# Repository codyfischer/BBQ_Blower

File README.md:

# BBQ_Blower
PCB to control relays, mosfet's, measure temperature wirelessly using ESP8266 and Lora Wan

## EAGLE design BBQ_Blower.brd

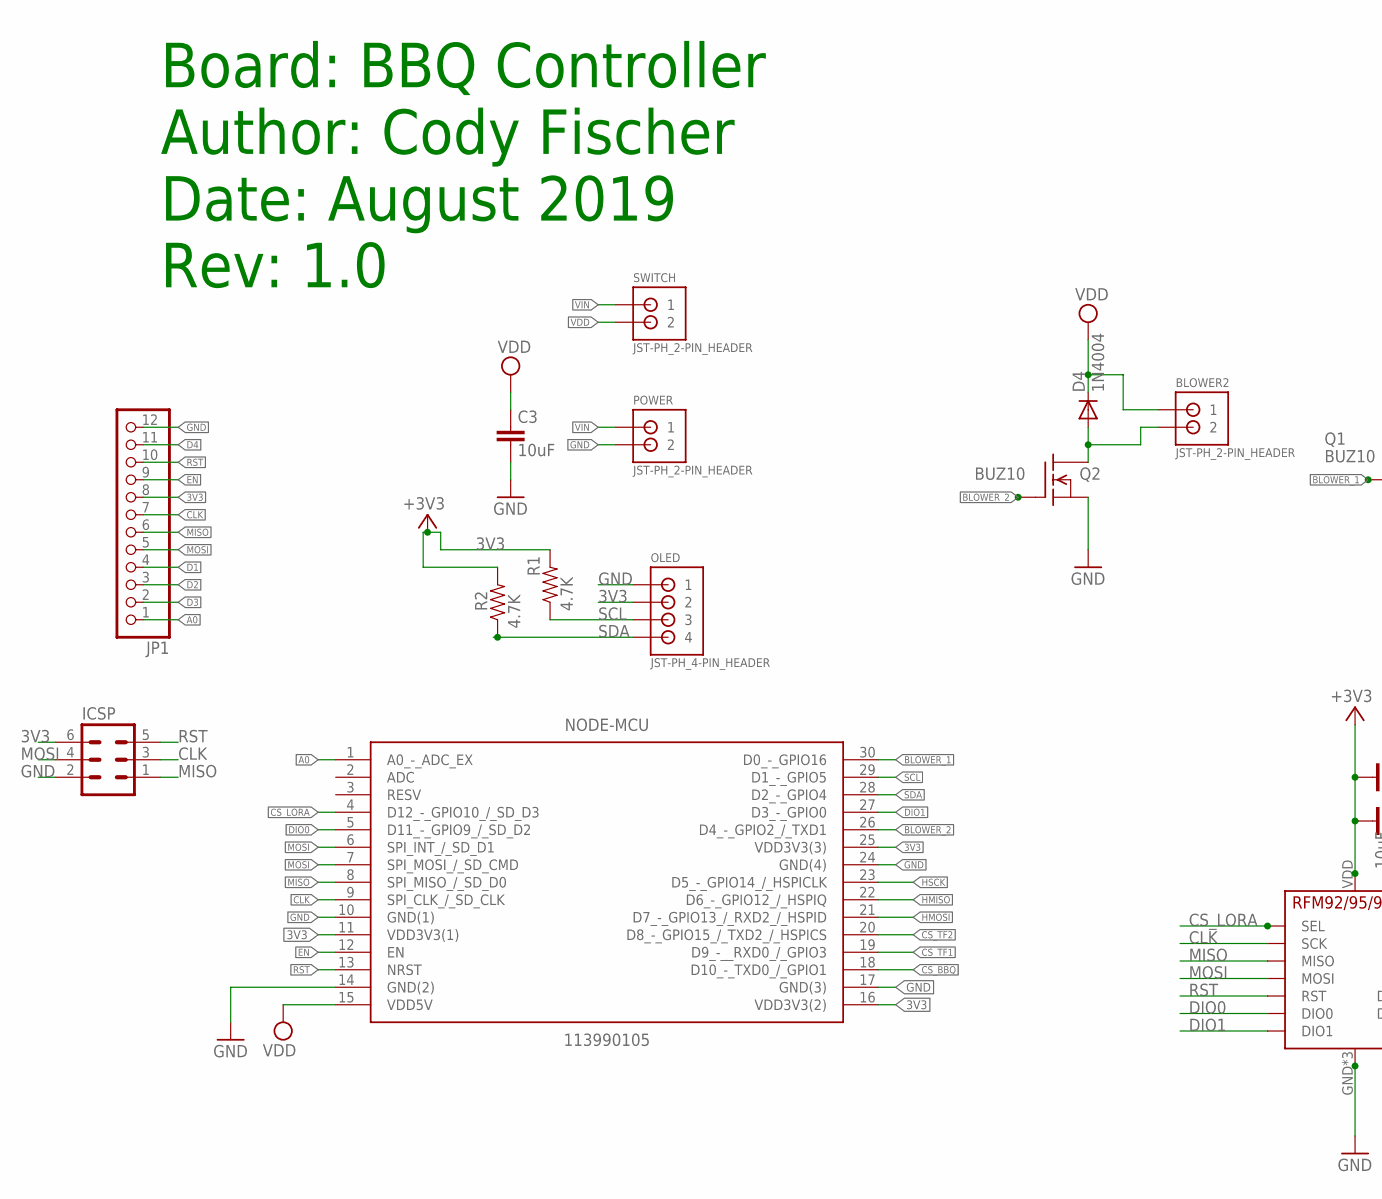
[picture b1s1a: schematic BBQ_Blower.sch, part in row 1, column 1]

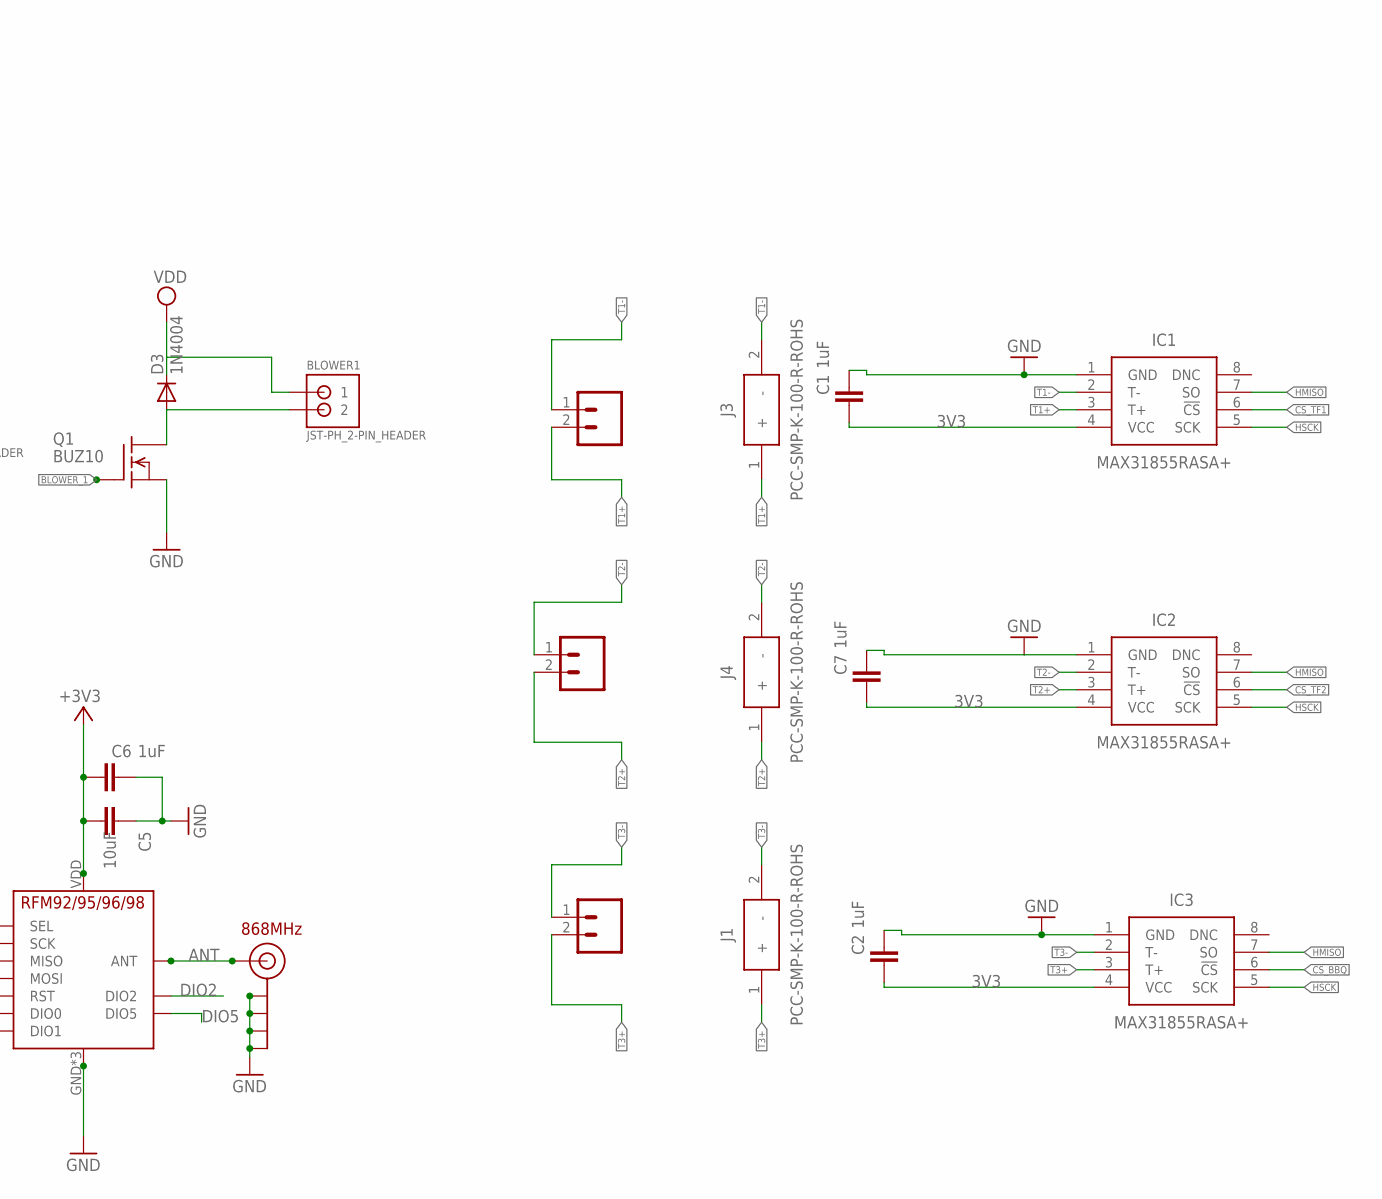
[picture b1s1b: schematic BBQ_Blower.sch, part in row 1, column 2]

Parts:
BLOWER1, BLOWER2: JST-PH_2-PIN_HEADER; JST_B2B-PH_HEADER
C1, C2, C6, C7: 1uF; C0805K
C3: 10uF; C025-050X050
C5: 10uF; C0805K
D3, D4: 1N4004; DO41-10
IC1, IC2, IC3: MAX31855RASA+; SOIC127P600X175-8N
ICSP: MA03-2
J1, J3, J4: PCC-SMP-K-100-R-ROHS; PCC-SMP
J$2: ANTENNATINY; SMA_UFL_PAD_TINY
JP1: PINHD-1X12; 1X12
NODE-MCU: 113990105; DIP2286W64P254L4826H735Q30N
OLED: JST-PH_4-PIN_HEADER; JST_B4B-PH_HEADER
POWER: JST-PH_2-PIN_HEADER; JST_B2B-PH_HEADER
Q1, Q2: BUZ10; TO220
R1, R2: 4.7K; 0805-RES
SWITCH: JST-PH_2-PIN_HEADER; JST_B2B-PH_HEADER
TH1, TH2, TH3: CONN_025MM; SCREWTERMINAL-5MM-2
U$5: RFM95

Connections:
3V3: C1.2, C2.2, C5.2, C6.2, C7.2, IC1.4 (VCC), IC2.4 (VCC), IC3.4 (VCC), ICSP.6, JP1.8, NODE-MCU.11 (VDD3V3(1)), NODE-MCU.16 (VDD3V3(2)), NODE-MCU.25 (VDD3V3(3)), OLED.P2 (2), R1.2, R2.2, U$5.VDD (VCC)
A0: JP1.1, NODE-MCU.1 (A0_-_ADC_EX)
ANT: J$2.ANT1 (SIGNAL), J$2.ANT2 (SIGNAL), J$2.ANT3 (SIGNAL), U$5.ANT
BLOWER1: BLOWER2.P2 (2), D4.A, Q2.2 (D)
BLOWER2: BLOWER1.P2 (2), D3.A, Q1.2 (D)
BLOWER_1: NODE-MCU.30 (D0_-_GPIO16), Q1.1 (G)
BLOWER_2: NODE-MCU.26 (D4_-_GPIO2_/_TXD1), Q2.1 (G)
CLK: ICSP.3, JP1.7, NODE-MCU.9 (SPI_CLK_/_SD_CLK), U$5.SCK
CS_BBQ: IC3.6 (!CS), NODE-MCU.18 (D10_-_TXD0_/_GPIO1)
CS_LORA: NODE-MCU.4 (D12_-_GPIO10_/_SD_D3), U$5.NSS (SEL)
CS_TF1: IC1.6 (!CS), NODE-MCU.19 (D9_-__RXD0_/_GPIO3)
CS_TF2: IC2.6 (!CS), NODE-MCU.20 (D8_-_GPIO15_/_TXD2_/_HSPICS)
D1: JP1.4
D2: JP1.3
D3: JP1.2
D4: JP1.11
DIO0: NODE-MCU.5 (D11_-_GPIO9_/_SD_D2), U$5.DIO0
DIO1: NODE-MCU.27 (D3_-_GPIO0), U$5.DIO1
DIO2: U$5.DIO2
DIO5: U$5.DIO5
EN: JP1.9, NODE-MCU.12 (EN)
GND: C1.1, C2.1, C3.2, C5.1, C6.1, C7.1, IC1.1 (GND), IC2.1 (GND), IC3.1 (GND), ICSP.2, J$2.GND1 (GND), J$2.GND2 (GND), J$2.GND3 (GND), J$2.GND4 (GND), JP1.12, NODE-MCU.10 (GND(1)), NODE-MCU.14 (GND(2)), NODE-MCU.17 (GND(3)), NODE-MCU.24 (GND(4)), OLED.P1 (1), POWER.P2 (2), Q1.3 (S), Q2.3 (S), U$5.GND, U$5.GND1 (GND), U$5.GND2 (GND)
HMISO: IC1.7 (SO), IC2.7 (SO), IC3.7 (SO), NODE-MCU.22 (D6_-_GPIO12_/_HSPIQ)
HMOSI: NODE-MCU.21 (D7_-_GPIO13_/_RXD2_/_HSPID)
HSCK: IC1.5 (SCK), IC2.5 (SCK), IC3.5 (SCK), NODE-MCU.23 (D5_-_GPIO14_/_HSPICLK)
MISO: ICSP.1, JP1.6, NODE-MCU.8 (SPI_MISO_/_SD_D0), U$5.MISO
MOSI: ICSP.4, JP1.5, NODE-MCU.6 (SPI_INT_/_SD_D1), NODE-MCU.7 (SPI_MOSI_/_SD_CMD), U$5.MOSI
RST: ICSP.5, JP1.10, NODE-MCU.13 (NRST), U$5.RST
SCL: NODE-MCU.29 (D1_-_GPIO5), OLED.P3 (3), R1.1
SDA: NODE-MCU.28 (D2_-_GPIO4), OLED.P4 (4), R2.1
T1+: IC1.3 (T+), J3.1 (+), TH3.2
T1-: IC1.2 (T-), J3.2 (-), TH3.1
T2+: IC2.3 (T+), J4.1 (+), TH2.2
T2-: IC2.2 (T-), J4.2 (-), TH2.1
T3+: IC3.3 (T+), J1.1 (+), TH1.2
T3-: IC3.2 (T-), J1.2 (-), TH1.1
VDD: BLOWER1.P1 (1), BLOWER2.P1 (1), C3.1, D3.C, D4.C, NODE-MCU.15 (VDD5V), SWITCH.P2 (2)
VIN: POWER.P1 (1), SWITCH.P1 (1)

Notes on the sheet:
868MHz
Board: BBQ Controller Author: Cody Fischer Date: August 2019 Rev: 1.0

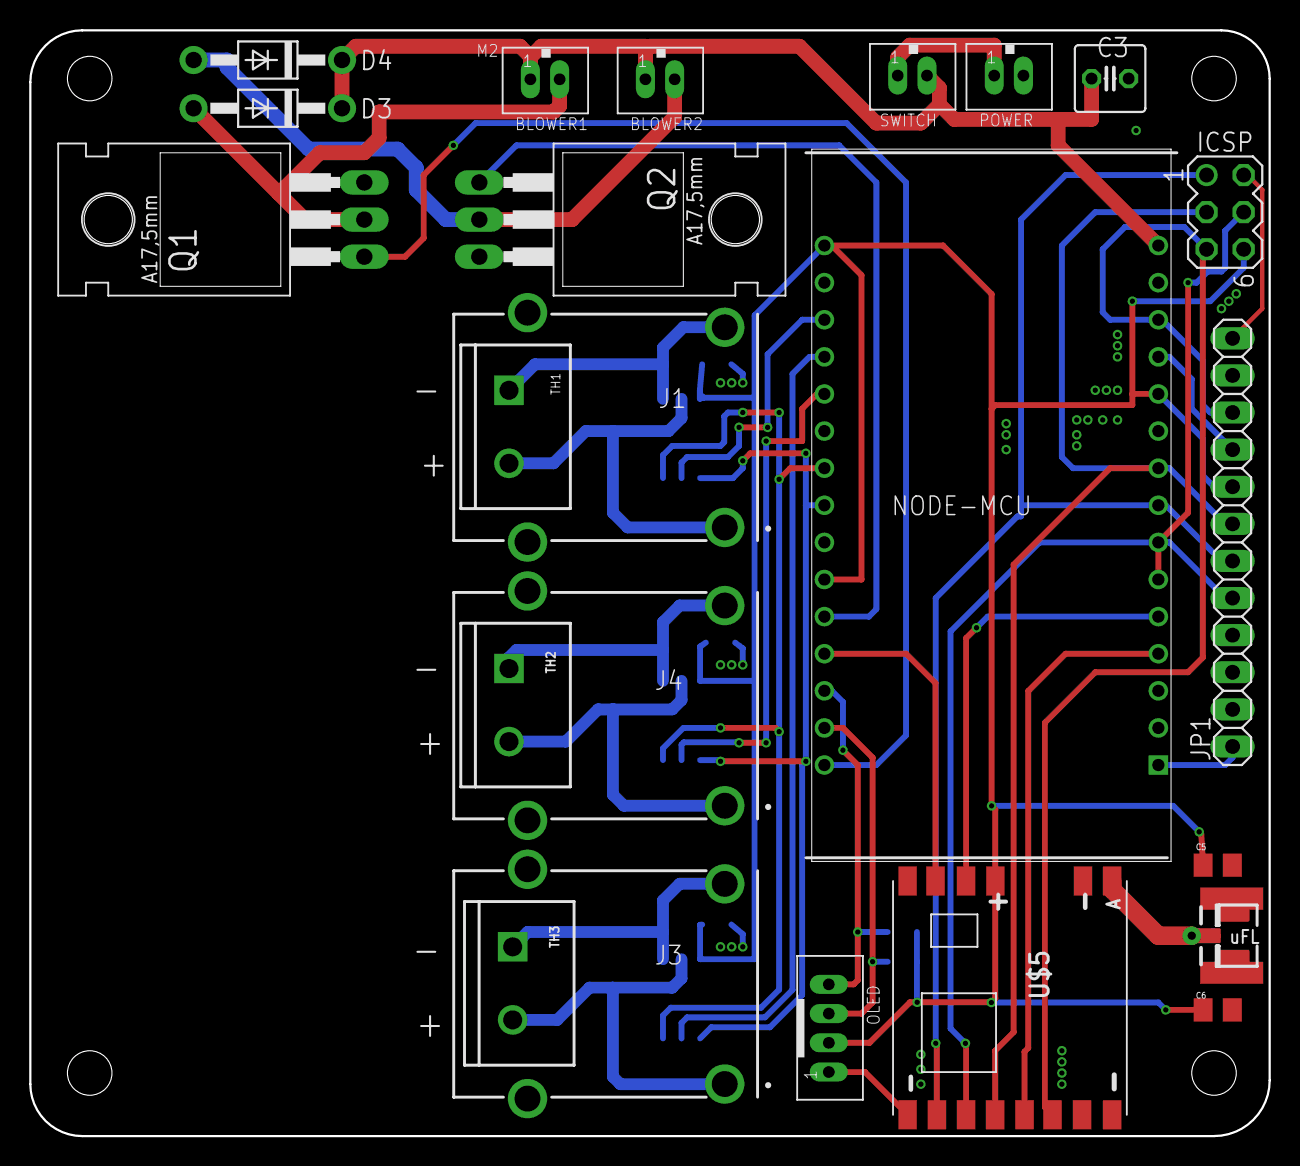
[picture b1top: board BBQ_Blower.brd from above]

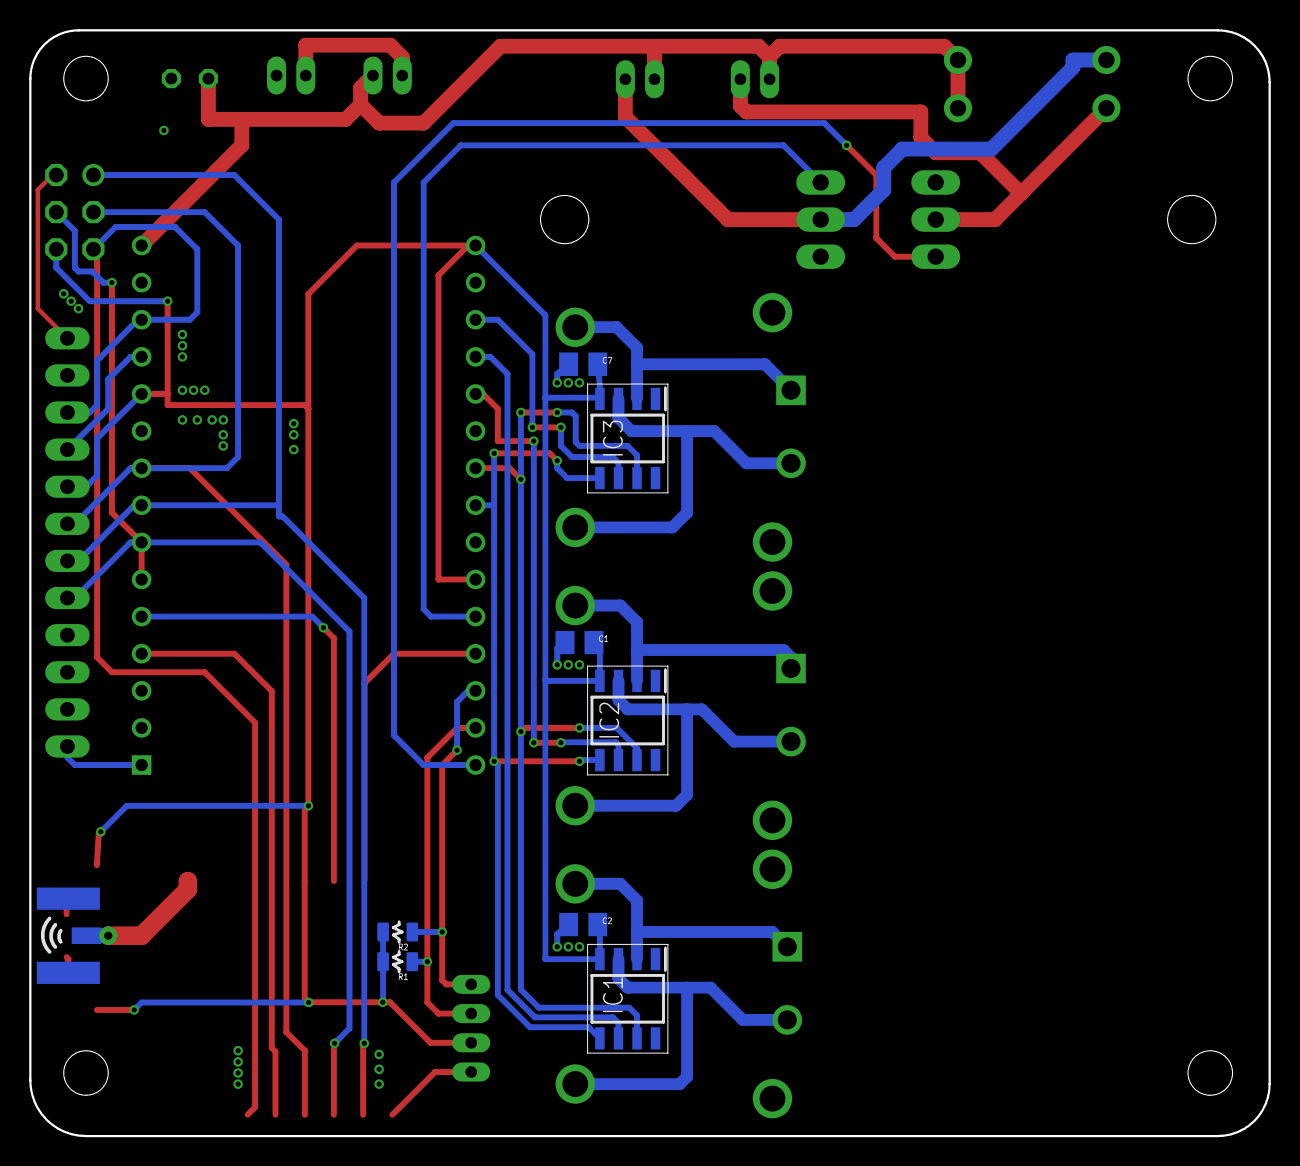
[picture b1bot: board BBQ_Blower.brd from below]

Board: 2 copper layers, 84.8 x 75.7 mm, 31 parts (8 on the bottom side), 31 nets.

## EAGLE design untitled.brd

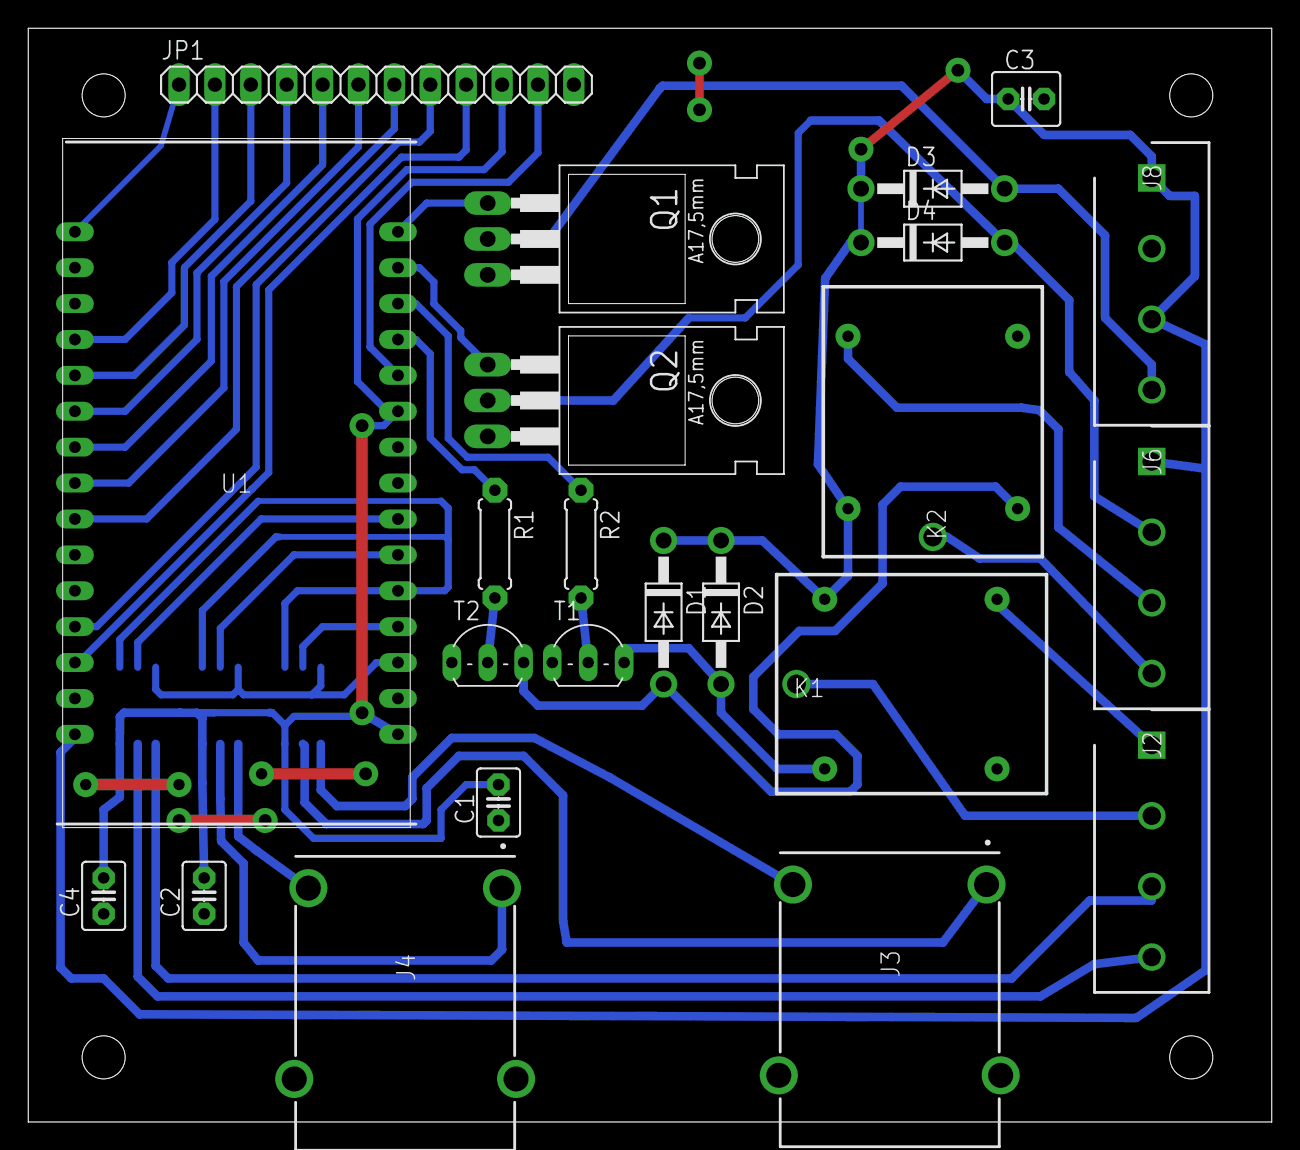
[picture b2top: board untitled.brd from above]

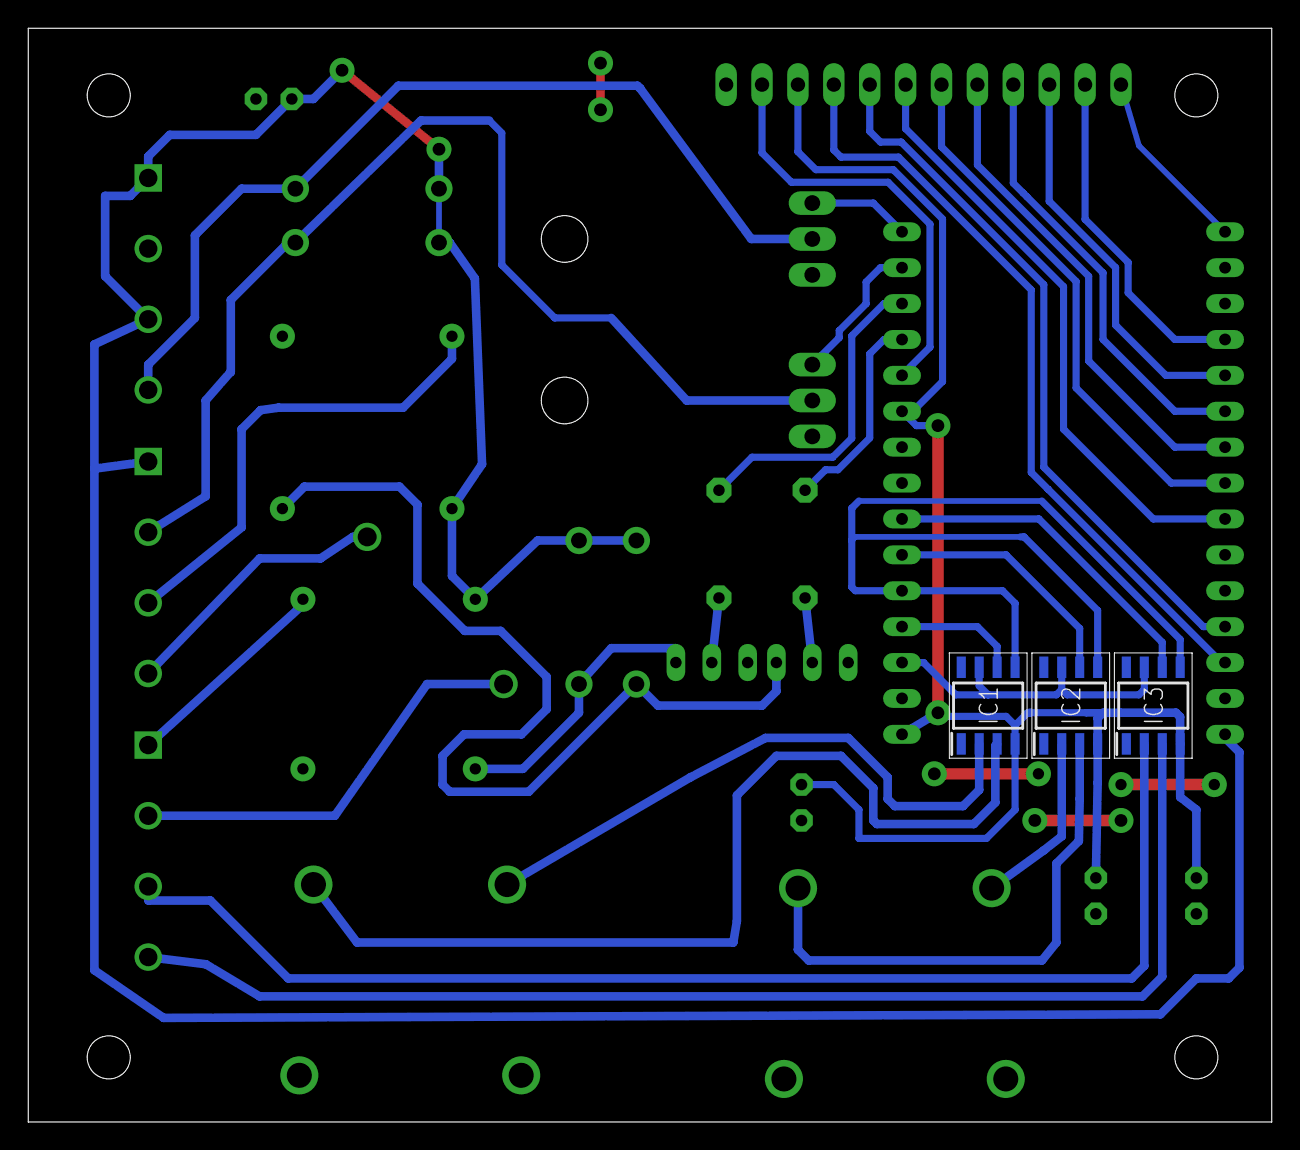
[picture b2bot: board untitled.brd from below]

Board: 2 copper layers, 88.0 x 77.4 mm, 26 parts (3 on the bottom side), 38 nets.

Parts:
C1, C2, C4: C2.5-3
C3: C2.5-4
D1, D2, D3, D4: 1N4004; DO41-10
IC1, IC2, IC3: MAX31855RASA+; SOIC127P600X175-8N
J2, J6, J8: 1729034; SHDR4W110P0X500_1X4_2000X810X1
J3, J4: PCC-SMP-K-100-R-ROHS; PCC-SMP
JP1: 1X12
K1, K2: SRD-12VDC-SL-C; SRD
Q1, Q2: BUZ10; TO220
R1, R2: 0207/7
T1, T2: 2N2222; TO92-EBC-OVAL
U1: 113990105; DIP2286W64P254L4826H735Q30N

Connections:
3V3: C1.2, C2.2, C4.2, IC1.4, IC2.4, IC3.4, JP1.10, U1.16, U1.25
A0: JP1.1, U1.1
BLOWER1: D3.A, J8.4, Q1.2
BLOWER2: D4.A, J6.2, Q2.2
BLOWER_1: Q1.1, U1.30
BLOWER_2: Q2.1, U1.29
CLK: JP1.7, U1.9
CMD: JP1.5, U1.7
CS_1: IC1.6, U1.19
CS_2: IC2.6, U1.21
CS_3: IC3.6, U1.22
D0: JP1.6, U1.8
D1: JP1.4, U1.6
D2: JP1.3, U1.5
D3: JP1.2, U1.4
D4: JP1.11, U1.26
EN: JP1.8, U1.12
GND: C1.1, C2.1, C3.2, C4.1, IC1.1, IC2.1, IC3.1, J8.2, JP1.12, Q1.3, Q2.3, T1.E, T2.E, U1.14, U1.17
unnamed: R1.2, T2.B
unnamed: D1.A, K2.3, T2.C
unnamed: R2.2, T1.B
unnamed: D2.A, K1.3, T1.C
RELAY1(+): J2.1, K1.4
RELAY1(-): J2.2, K1.1
RELAY2(+): J6.3, K2.4
RELAY2(-): J6.4, K2.1
RELAY_1: R2.1, U1.28
RELAY_2: R1.1, U1.27
RST: JP1.9, U1.13
SCK: IC1.5, IC2.5, IC3.5, U1.20
SO: IC1.7, IC2.7, IC3.7, U1.18
T1+: IC1.3, J3.1
T1-: IC1.2, J3.2
T2+: IC2.3, J4.1
T2-: IC2.2, J4.2
T3+: IC3.3, J2.4
T3-: IC3.2, J2.3
VDD: C3.1, D1.C, D2.C, D3.C, D4.C, J6.1, J8.1, J8.3, K1.2, K2.2, U1.15

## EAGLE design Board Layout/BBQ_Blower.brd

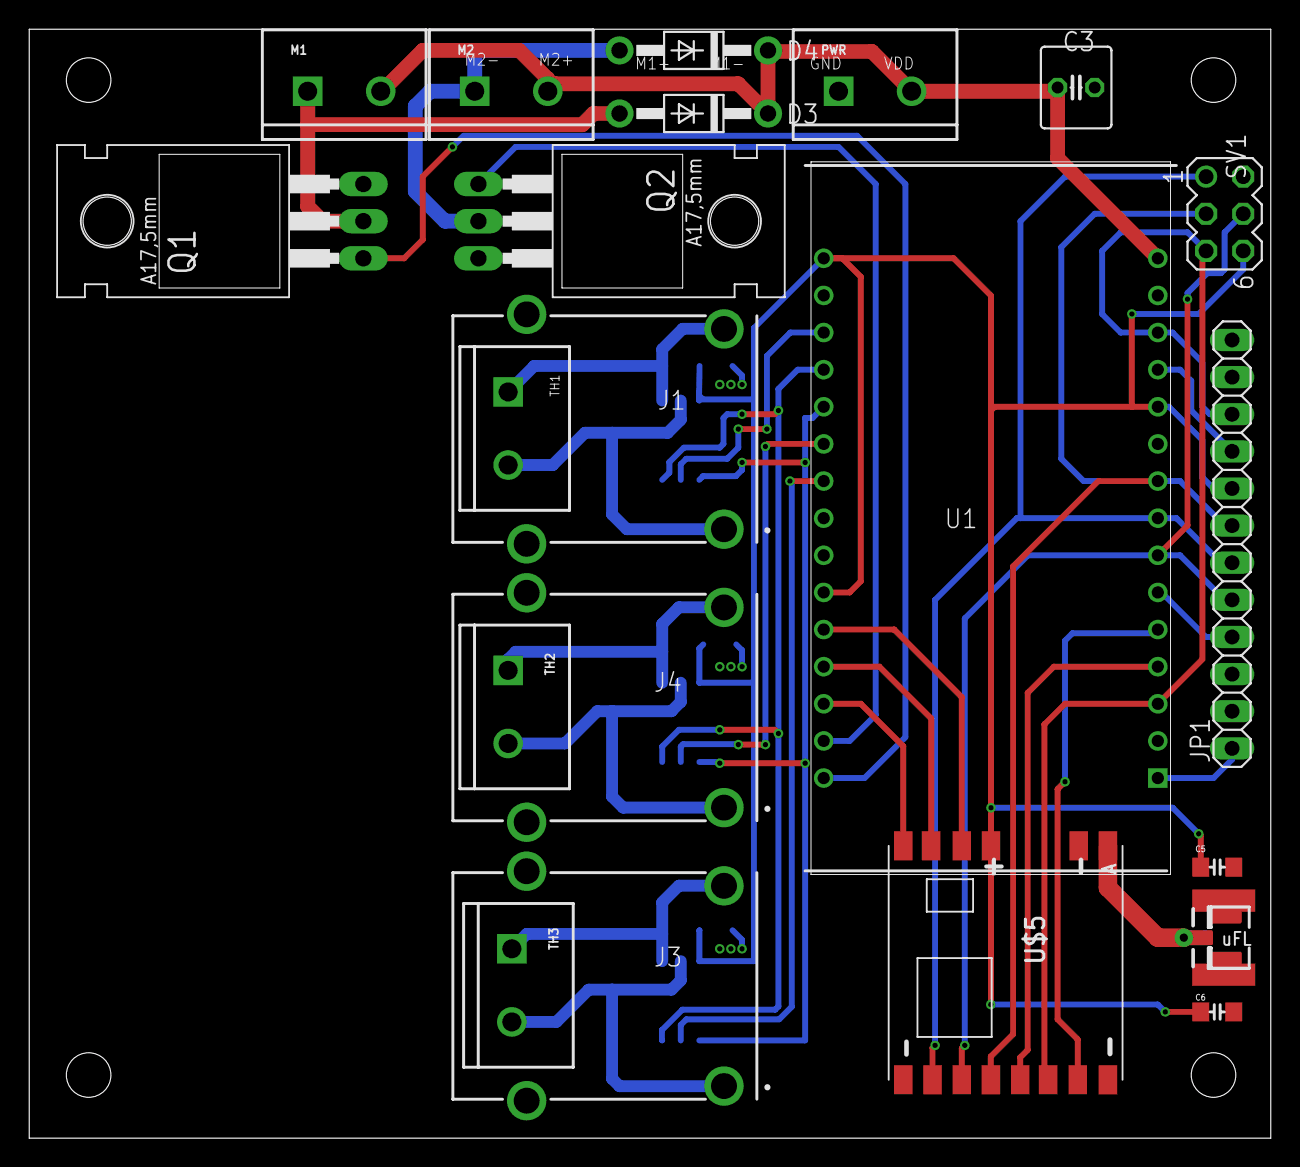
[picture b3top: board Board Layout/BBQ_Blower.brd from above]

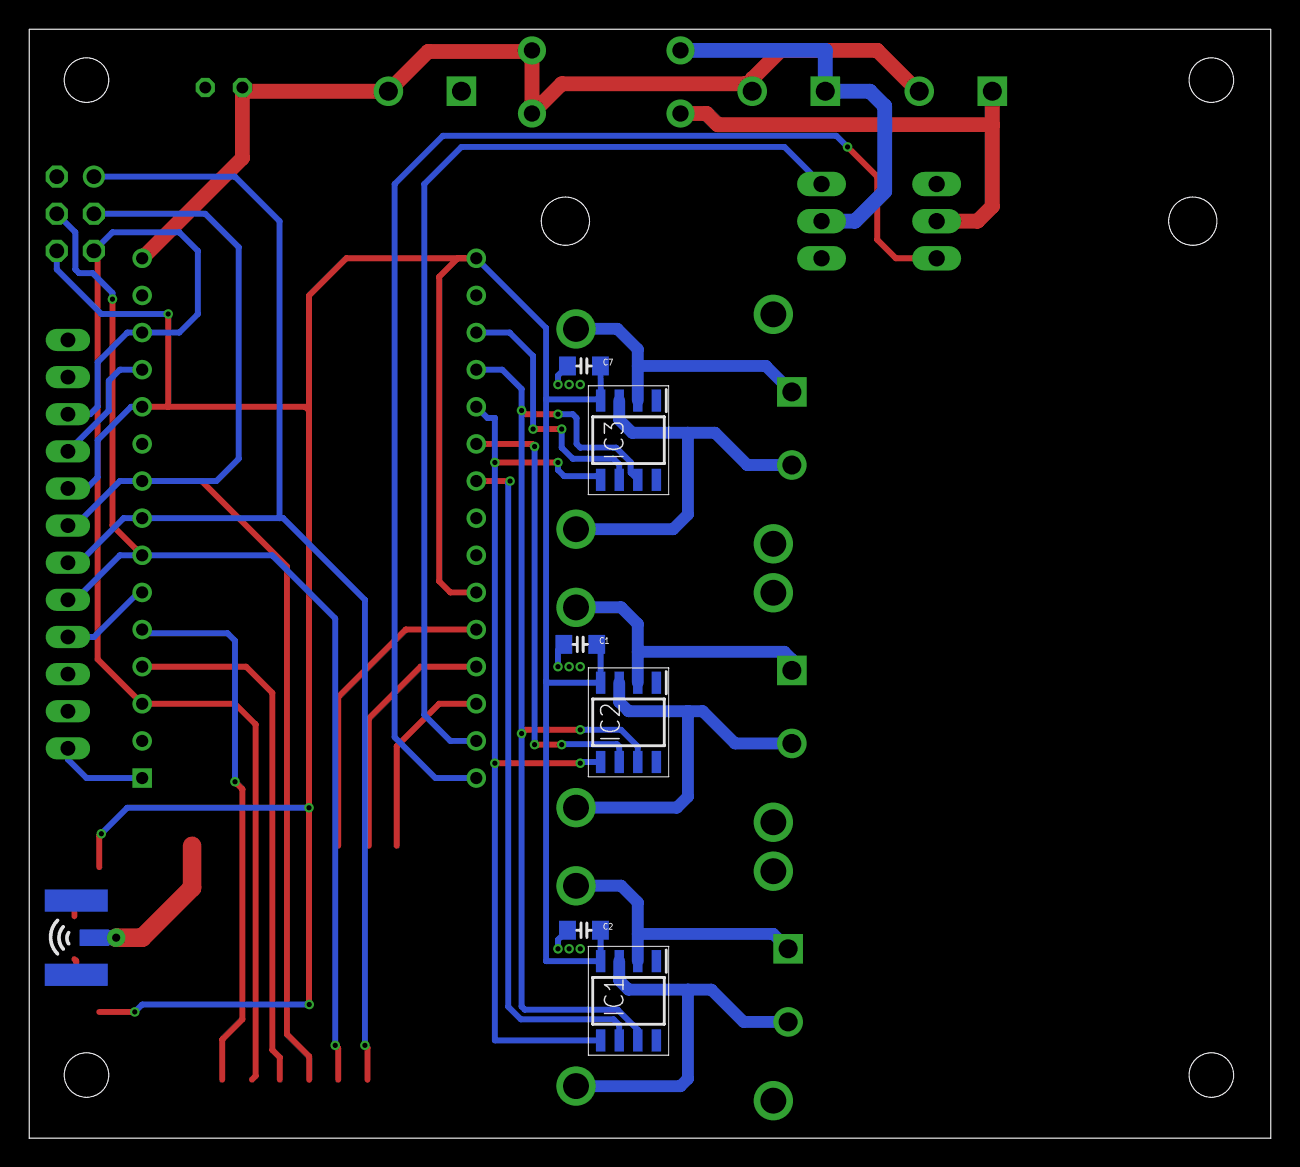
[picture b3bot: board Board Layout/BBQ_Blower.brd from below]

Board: 2 copper layers, 84.9 x 75.9 mm, 27 parts (6 on the bottom side), 31 nets.

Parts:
C1, C2, C6, C7: 1uF; 0805-CAP-LARGEPADS
C3: C025-060X050
C5: 10uF; 0805-CAP-LARGEPADS
D3, D4: 1N4004; DO41-10
IC1, IC2, IC3: MAX31855RASA+; SOIC127P600X175-8N
J1, J3, J4: PCC-SMP-K-100-R-ROHS; PCC-SMP
J$2: ANTENNATINY; SMA_UFL_PAD_TINY
JP1: 1X12
M1, M2: SCREWTERMINAL-5MM-2
PWR: SCREWTERMINAL-5MM-2
Q1, Q2: BUZ10; TO220
SV1: MA03-2
TH1, TH2, TH3: SCREWTERMINAL-5MM-2
U1: 113990105; DIP2286W64P254L4826H735Q30N
U$5: RFM95

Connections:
3V3: C1.2, C2.2, C5.2, C6.2, C7.2, IC1.4, IC2.4, IC3.4, JP1.8, SV1.6, U1.11, U1.16, U1.25, U$5.VDD
A0: JP1.1, U1.1
ANT: J$2.ANT1, J$2.ANT2, J$2.ANT3, U$5.ANT
BLOWER1: D4.A, M2.1, Q2.2
BLOWER2: D3.A, M1.1, Q1.2
BLOWER_1: Q1.1, U1.30
BLOWER_2: Q2.1, U1.29
CLK: JP1.7, SV1.3, U1.9, U$5.SCK
CS_1: IC1.6, U1.22
CS_2: IC2.6, U1.21
CS_3: IC3.6, U1.18
CS_LORA: U1.4, U$5.NSS
D1: JP1.4, U1.6
DIO0: U1.26, U$5.DIO0
DIO1: U1.27, U$5.DIO1
DIO2: U1.28, U$5.DIO2
DIO5: U1.5, U$5.DIO5
EN: JP1.9, U1.12
GND: C1.1, C2.1, C3.2, C5.1, C6.1, C7.1, IC1.1, IC2.1, IC3.1, J$2.GND1, J$2.GND2, J$2.GND3, J$2.GND4, JP1.12, PWR.1, Q1.3, Q2.3, SV1.2, U1.14, U1.17, U$5.GND, U$5.GND1, U$5.GND2
MISO: JP1.6, SV1.1, U1.8, U$5.MISO
MOSI: JP1.5, SV1.4, U1.7, U$5.MOSI
RST: JP1.10, SV1.5, U1.3, U1.13, U$5.RST
SCK: IC1.5, IC2.5, IC3.5, U1.20
SO: IC1.7, IC2.7, IC3.7, U1.19
T1+: IC1.3, J3.1, TH3.2
T1-: IC1.2, J3.2, TH3.1
T2+: IC2.3, J4.1, TH2.2
T2-: IC2.2, J4.2, TH2.1
T3+: IC3.3, J1.1, TH1.2
T3-: IC3.2, J1.2, TH1.1
VDD: C3.1, D3.C, D4.C, M1.2, M2.2, PWR.2, U1.15

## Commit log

2019-07-22 initial
2019-07-22 zip test
2019-07-22 deleted zip
2019-07-22 initial Lora
2019-07-22 initial files
2019-07-22 added Lora Component
2019-07-22 minor change
2019-07-23 Removed Relay
2019-07-23 traces
2019-07-24 new layout
2019-07-24 changed a wire
2019-07-29 re-arraging
2019-07-31 silk and wiring complete
2019-08-08 moved header
2019-08-14 restructured files
2019-08-14 cleaned structure
2019-08-28 rounded corners
2019-09-05 first final
2020-07-02 cody

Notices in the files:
parts and their libraries:
SparkFun-Connectors: Licensing: Creative Commons ShareAlike 4.0 International - https://creativecommons.org/licenses/by-sa/4.0
